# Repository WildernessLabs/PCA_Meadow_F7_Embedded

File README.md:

# PCA_Meadow_F7_Embedded
PCA (Printed Circuit Assembly) design of the Meadow F7 Embedded SMT module.\
Tool: Kicad\
Version: 5.1.6\
Current Revision: B

## Folder Structure
### Home Folder
* Source Files for Current Revsion
### PCB_FAB
Files Required to make the bare PCB
* Gerbers
* Gerbers (zip)
* Stack up 
* Fab Drawing (pdf)
* Pannel Gerbers (to be added)
* Netlist(.d356)
### Assembly
Files required to asseble the PCA, using the bare PCB.
* BOM
* PDF Schematic
* Assembly Drawing (pdf)
* Rendered Pictures
* 3D Model
* pick and place file/pos file (.csv)

## Rev B Change Log
* Retuned USB signals
* Added edge plating to module SMT pads
* Created Fab drawing with pcb fab notes
* Created Assembly Drawing, added assembly notes to it

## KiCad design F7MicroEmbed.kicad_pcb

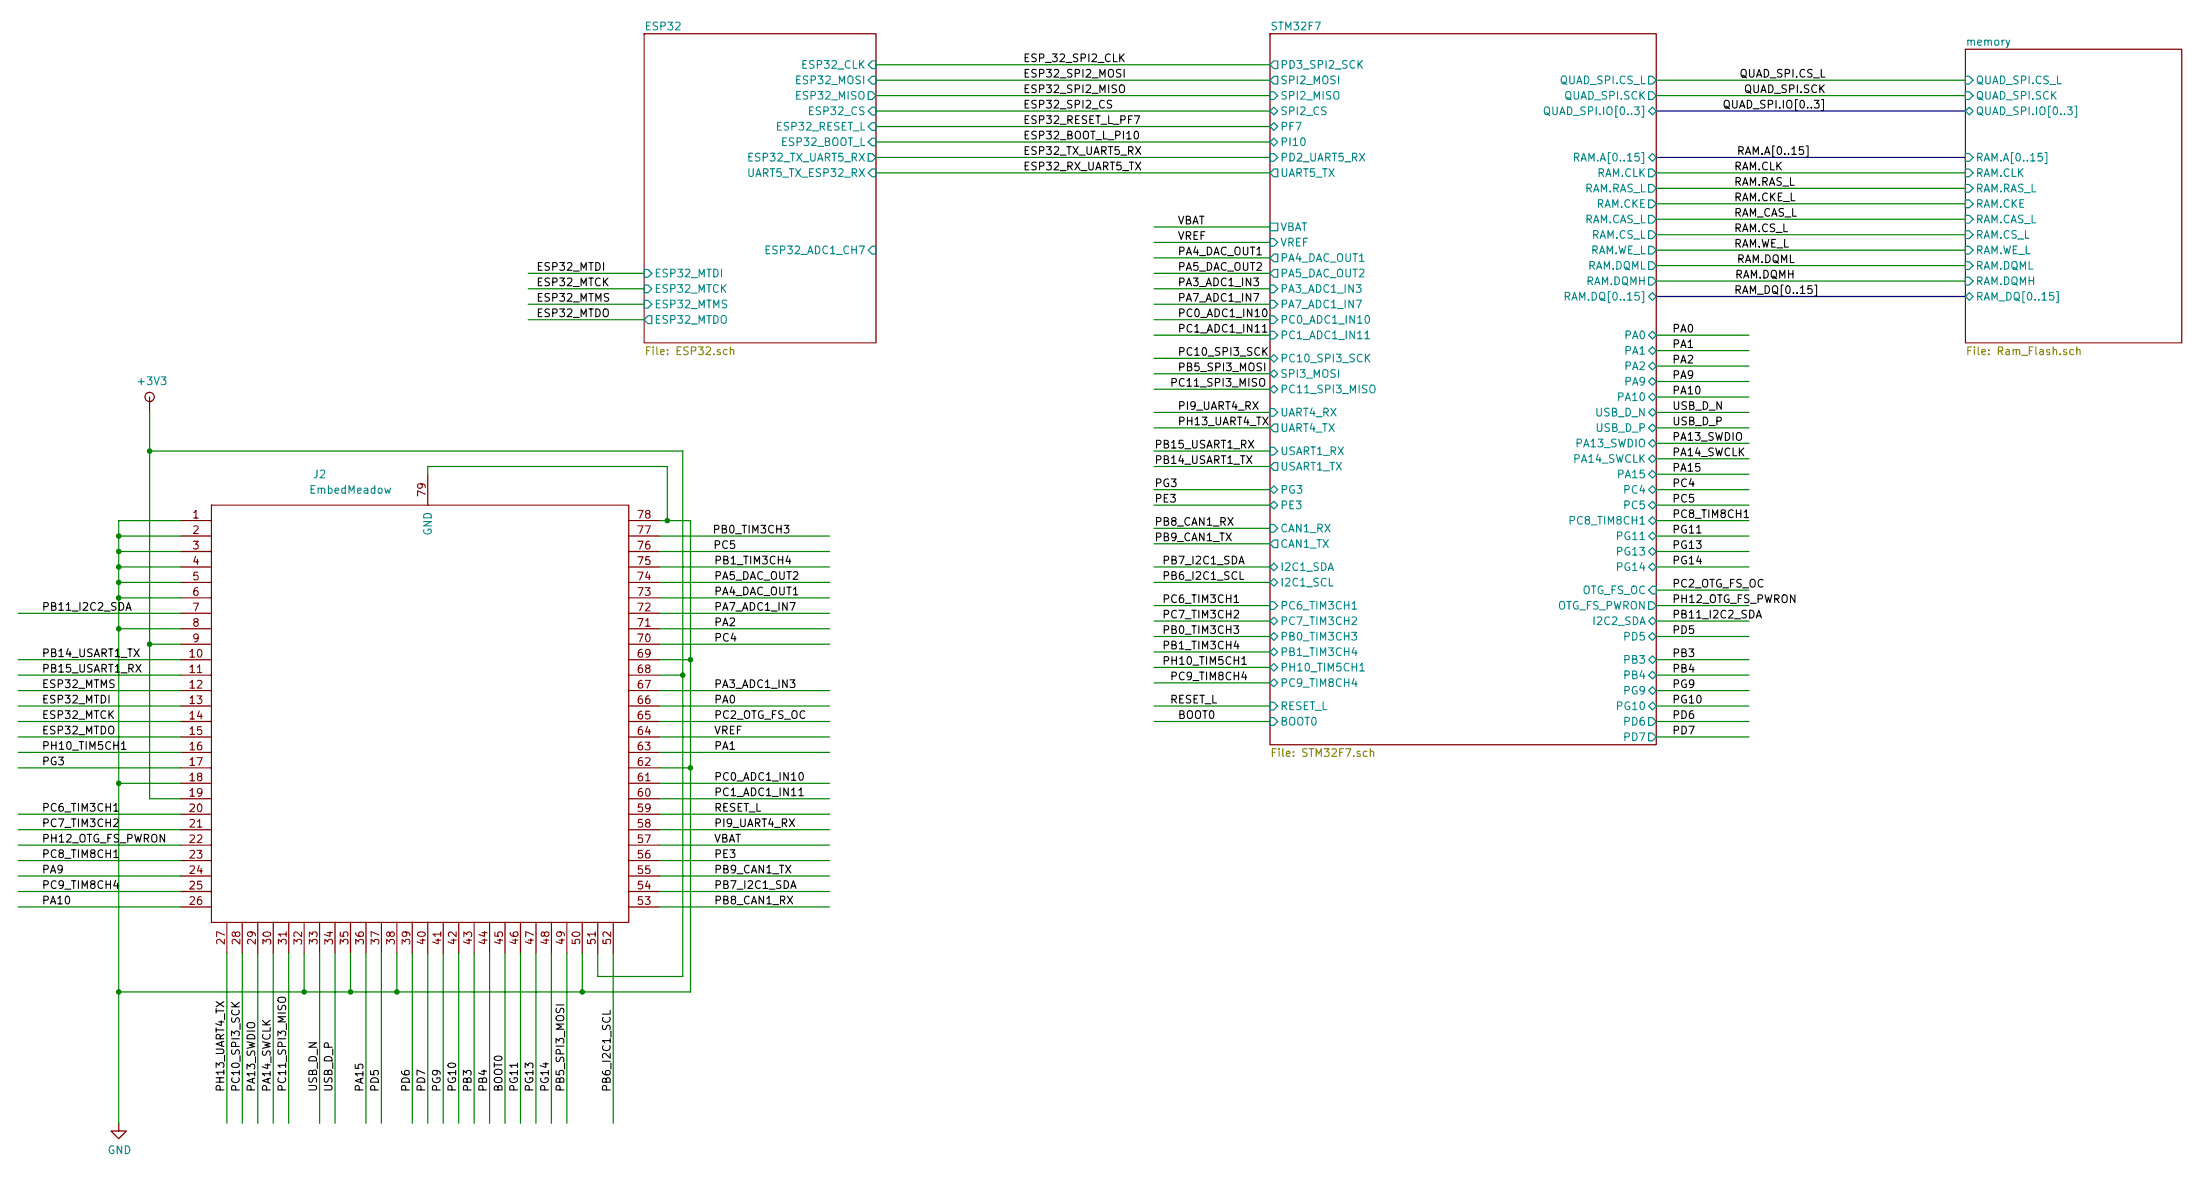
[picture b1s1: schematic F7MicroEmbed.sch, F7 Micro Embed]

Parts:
J2: EmbedMeadow; MeadowEmbeded_OnModule

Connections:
+3V3: J2.9, J2.19, J2.51, J2.68; also elsewhere on the board
/BOOT0: J2.45; also elsewhere on the board
/ESP32_MTCK: J2.14; also elsewhere on the board
/ESP32_MTDI: J2.13; also elsewhere on the board
/ESP32_MTDO: J2.15; also elsewhere on the board
/ESP32_MTMS: J2.12; also elsewhere on the board
/PA0: J2.66; also elsewhere on the board
/PA1: J2.63; also elsewhere on the board
/PA2: J2.71; also elsewhere on the board
/PA3_ADC1_IN3: J2.67; also elsewhere on the board
/PA4_DAC_OUT1: J2.73; also elsewhere on the board
/PA5_DAC_OUT2: J2.74; also elsewhere on the board
/PA7_ADC1_IN7: J2.72; also elsewhere on the board
/PA9: J2.24; also elsewhere on the board
/PA10: J2.26; also elsewhere on the board
/PA13_SWDIO: J2.29; also elsewhere on the board
/PA14_SWCLK: J2.30; also elsewhere on the board
/PA15: J2.36; also elsewhere on the board
/PB0_TIM3CH3: J2.77; also elsewhere on the board
/PB1_TIM3CH4: J2.75; also elsewhere on the board
/PB3: J2.43; also elsewhere on the board
/PB4: J2.44; also elsewhere on the board
/PB5_SPI3_MOSI: J2.49; also elsewhere on the board
/PB6_I2C1_SCL: J2.52; also elsewhere on the board
/PB7_I2C1_SDA: J2.54; also elsewhere on the board
/PB8_CAN1_RX: J2.53; also elsewhere on the board
/PB9_CAN1_TX: J2.55; also elsewhere on the board
/PB11_I2C2_SDA: J2.7; also elsewhere on the board
/PB14_USART1_TX: J2.10; also elsewhere on the board
/PB15_USART1_RX: J2.11; also elsewhere on the board
/PC0_ADC1_IN10: J2.61; also elsewhere on the board
/PC1_ADC1_IN11: J2.60; also elsewhere on the board
/PC2_OTG_FS_OC: J2.65; also elsewhere on the board
/PC4: J2.70; also elsewhere on the board
/PC5: J2.76; also elsewhere on the board
/PC6_TIM3CH1: J2.20; also elsewhere on the board
/PC7_TIM3CH2: J2.21; also elsewhere on the board
/PC8_TIM8CH1: J2.23; also elsewhere on the board
/PC9_TIM8CH4: J2.25; also elsewhere on the board
/PC10_SPI3_SCK: J2.28; also elsewhere on the board
/PC11_SPI3_MISO: J2.31; also elsewhere on the board
/PD5: J2.37; also elsewhere on the board
/PD6: J2.39; also elsewhere on the board
/PD7: J2.40; also elsewhere on the board
/PE3: J2.56; also elsewhere on the board
/PG3: J2.17; also elsewhere on the board
/PG9: J2.41; also elsewhere on the board
/PG10: J2.42; also elsewhere on the board
/PG11: J2.46; also elsewhere on the board
/PG13: J2.47; also elsewhere on the board
/PG14: J2.48; also elsewhere on the board
/PH10_TIM5CH1: J2.16; also elsewhere on the board
/PH12_OTG_FS_PWRON: J2.22; also elsewhere on the board
/PH13_UART4_TX: J2.27; also elsewhere on the board
/PI9_UART4_RX: J2.58; also elsewhere on the board
/RESET_L: J2.59; also elsewhere on the board
/USB_D_N: J2.33; also elsewhere on the board
/USB_D_P: J2.34; also elsewhere on the board
/VBAT: J2.57; also elsewhere on the board
/VREF: J2.64; also elsewhere on the board
GND: J2.1, J2.2, J2.3, J2.4, J2.5, J2.6, J2.8, J2.18, J2.32, J2.35, J2.38, J2.50, J2.62, J2.69, J2.78, J2.79 (GND); also elsewhere on the board

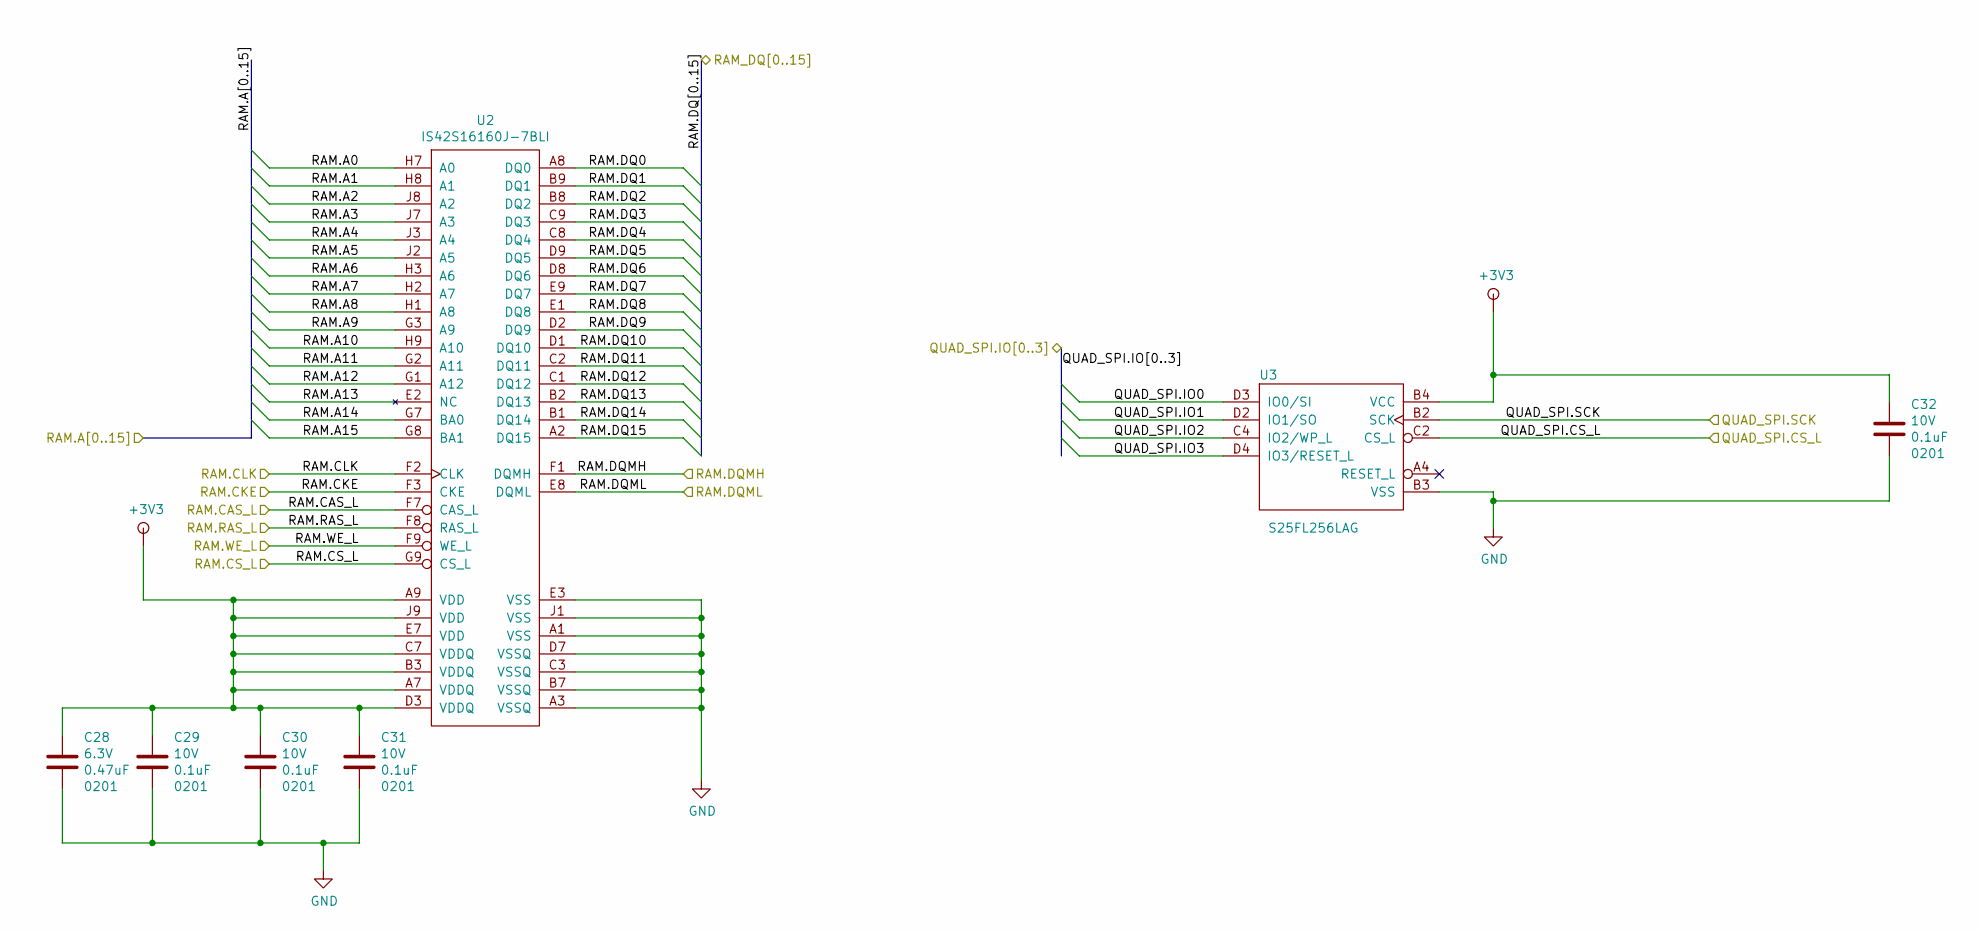
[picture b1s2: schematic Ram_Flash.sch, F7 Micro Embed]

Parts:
C28: C_0201_0.47UF_6.3V_X5R; C_0201; Voltage 6.3V; Tolerance 10%
C29, C30, C31, C32: C_0201_0.1UF_10V_X5R; C_0201; Voltage 10V; Tolerance 10%
U2: IS42S16160J-7BLI; TFBGA-54
U3: S25FL256LAG; BGA24C100P6X4_800X600X120N

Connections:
+3V3: C28.1, C29.1, C30.1, C31.1, C32.1, U2.A7 (VDDQ), U2.A9 (VDD), U2.B3 (VDDQ), U2.C7 (VDDQ), U2.D3 (VDDQ), U2.E7 (VDD), U2.J9 (VDD), U3.B4 (VCC); also elsewhere on the board
/QUAD_SPI.CS_L: U3.C2 (CS_L); also elsewhere on the board
/QUAD_SPI.SCK: U3.B2 (SCK); also elsewhere on the board
/RAM.CKE_L: U2.F3 (CKE); also elsewhere on the board
/RAM.CLK: U2.F2 (CLK); also elsewhere on the board
/RAM.CS_L: U2.G9 (CS_L); also elsewhere on the board
/RAM.DQMH: U2.F1 (DQMH); also elsewhere on the board
/RAM.DQML: U2.E8 (DQML); also elsewhere on the board
/RAM.RAS_L: U2.F8 (RAS_L); also elsewhere on the board
/RAM.WE_L: U2.F9 (WE_L); also elsewhere on the board
/RAM_CAS_L: U2.F7 (CAS_L); also elsewhere on the board
/STM32F7/QUAD_SPI.IO0: U3.D3 (IO0/SI); also elsewhere on the board
/STM32F7/QUAD_SPI.IO1: U3.D2 (IO1/SO); also elsewhere on the board
/STM32F7/QUAD_SPI.IO2: U3.C4 (IO2/WP_L); also elsewhere on the board
/STM32F7/QUAD_SPI.IO3: U3.D4 (IO3/RESET_L); also elsewhere on the board
/STM32F7/RAM.A0: U2.H7 (A0); also elsewhere on the board
/STM32F7/RAM.A1: U2.H8 (A1); also elsewhere on the board
/STM32F7/RAM.A2: U2.J8 (A2); also elsewhere on the board
/STM32F7/RAM.A3: U2.J7 (A3); also elsewhere on the board
/STM32F7/RAM.A4: U2.J3 (A4); also elsewhere on the board
/STM32F7/RAM.A5: U2.J2 (A5); also elsewhere on the board
/STM32F7/RAM.A6: U2.H3 (A6); also elsewhere on the board
/STM32F7/RAM.A7: U2.H2 (A7); also elsewhere on the board
/STM32F7/RAM.A8: U2.H1 (A8); also elsewhere on the board
/STM32F7/RAM.A9: U2.G3 (A9); also elsewhere on the board
/STM32F7/RAM.A10: U2.H9 (A10); also elsewhere on the board
/STM32F7/RAM.A11: U2.G2 (A11); also elsewhere on the board
/STM32F7/RAM.A12: U2.G1 (A12); also elsewhere on the board
/STM32F7/RAM.A14: U2.G7 (BA0); also elsewhere on the board
/STM32F7/RAM.A15: U2.G8 (BA1); also elsewhere on the board
/STM32F7/RAM.DQ0: U2.A8 (DQ0); also elsewhere on the board
/STM32F7/RAM.DQ1: U2.B9 (DQ1); also elsewhere on the board
/STM32F7/RAM.DQ2: U2.B8 (DQ2); also elsewhere on the board
/STM32F7/RAM.DQ3: U2.C9 (DQ3); also elsewhere on the board
/STM32F7/RAM.DQ4: U2.C8 (DQ4); also elsewhere on the board
/STM32F7/RAM.DQ5: U2.D9 (DQ5); also elsewhere on the board
/STM32F7/RAM.DQ6: U2.D8 (DQ6); also elsewhere on the board
/STM32F7/RAM.DQ7: U2.E9 (DQ7); also elsewhere on the board
/STM32F7/RAM.DQ8: U2.E1 (DQ8); also elsewhere on the board
/STM32F7/RAM.DQ9: U2.D2 (DQ9); also elsewhere on the board
/STM32F7/RAM.DQ10: U2.D1 (DQ10); also elsewhere on the board
/STM32F7/RAM.DQ11: U2.C2 (DQ11); also elsewhere on the board
/STM32F7/RAM.DQ12: U2.C1 (DQ12); also elsewhere on the board
/STM32F7/RAM.DQ13: U2.B2 (DQ13); also elsewhere on the board
/STM32F7/RAM.DQ14: U2.B1 (DQ14); also elsewhere on the board
/STM32F7/RAM.DQ15: U2.A2 (DQ15); also elsewhere on the board
/memory/RAM.A13: U2.E2 (NC)
GND: C28.2, C29.2, C30.2, C31.2, C32.2, U2.A1 (VSS), U2.A3 (VSSQ), U2.B7 (VSSQ), U2.C3 (VSSQ), U2.D7 (VSSQ), U2.E3 (VSS), U2.J1 (VSS), U3.B3 (VSS); also elsewhere on the board

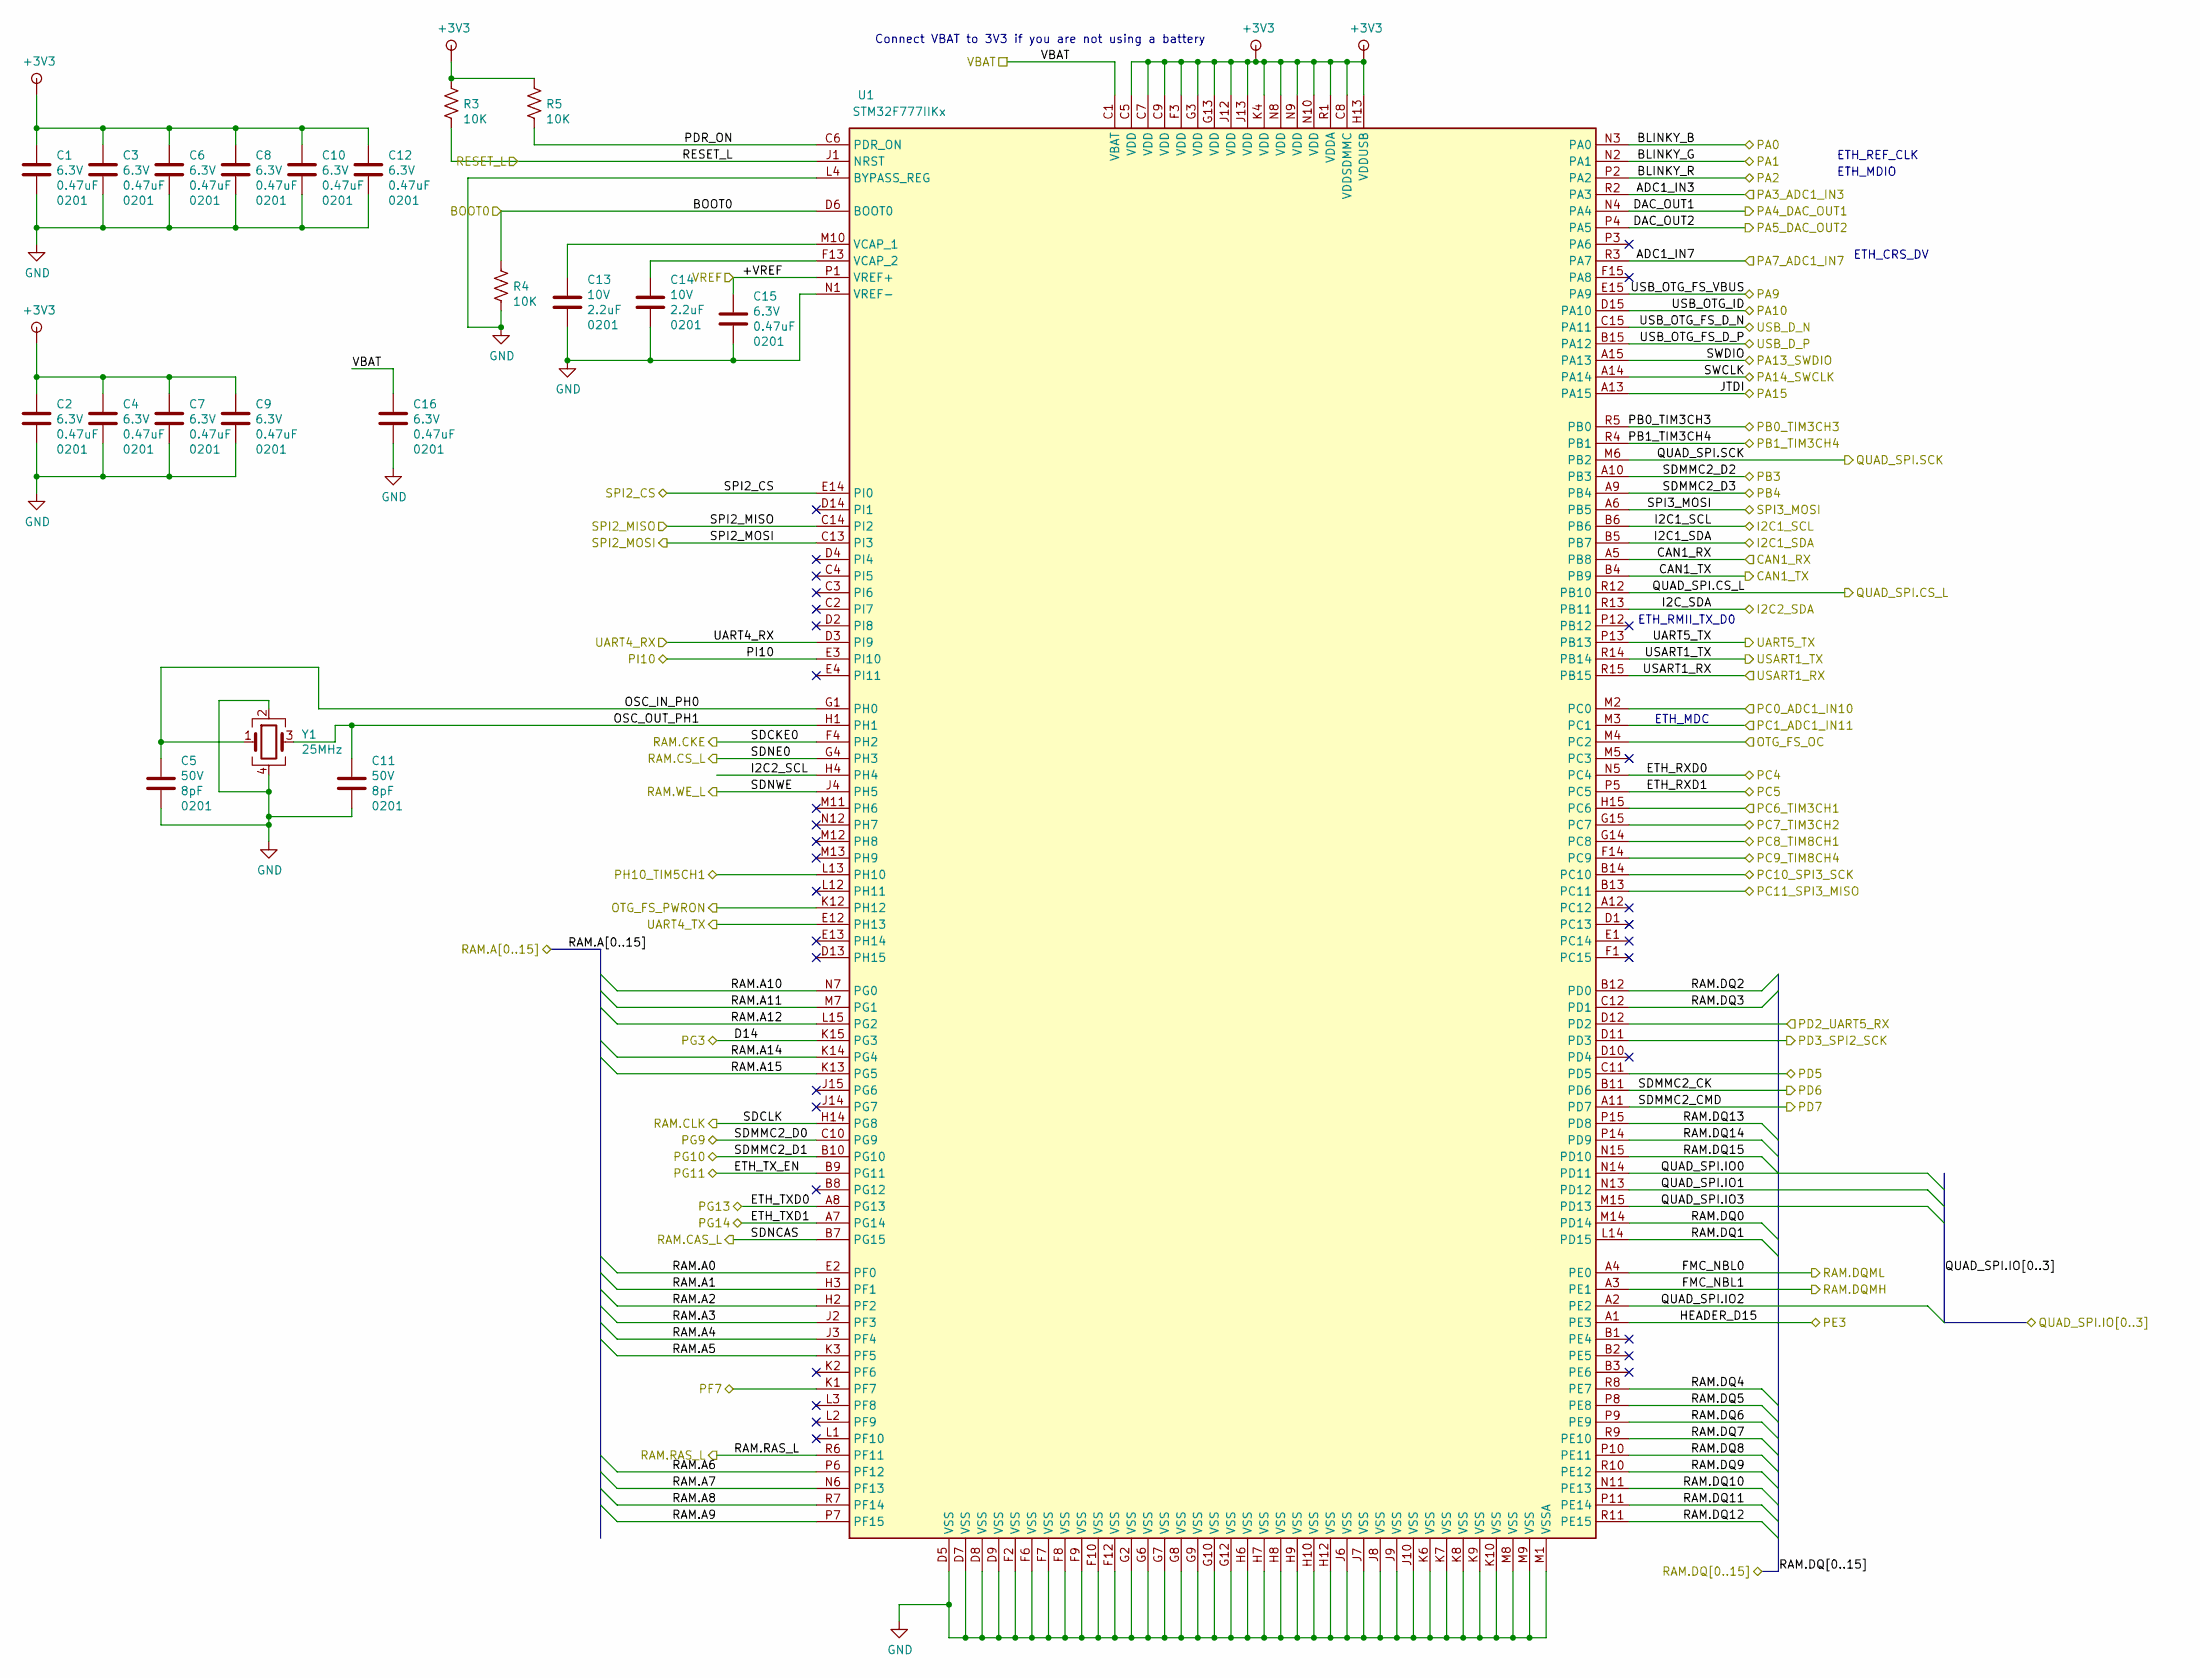
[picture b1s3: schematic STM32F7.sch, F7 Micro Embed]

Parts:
C1, C2, C3, C4, C6, C7, C8, C9, C10, C12, C15, C16: C_0201_0.47UF_6.3V_X5R; C_0201; Voltage 6.3V; Tolerance 10%
C5, C11: C_0201_8pF_50V_C0G; C_0201; Voltage 50V; Tolerance 0.5pF
C13, C14: C_0201_2.2UF_10V_X5R; C_0201; Voltage 10V; Tolerance 10%
R3, R4, R5: R_10K_1%_0201; R_0201
U1: STM32F777IIKx; UFBGA-201_10x10mm_Layout15x15_P0.65mm
Y1: ABM12W-25.0000MHZ-6-B1U-T3; XTAL_ABM12W-24.0000MHZ-6-B1U-T3

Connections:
+3V3: C1.1, C2.1, C3.1, C4.1, C6.1, C7.1, C8.1, C9.1, C10.1, C12.1, R3.1, R5.1, U1.C5 (VDD), U1.C7 (VDD), U1.C8 (VDDSDMMC), U1.C9 (VDD), U1.F3 (VDD), U1.G3 (VDD), U1.G13 (VDD), U1.H13 (VDDUSB), U1.J12 (VDD), U1.J13 (VDD), U1.K4 (VDD), U1.N8 (VDD), U1.N9 (VDD), U1.N10 (VDD), U1.R1 (VDDA); also elsewhere on the board
/BOOT0: R4.1, U1.D6 (BOOT0); also elsewhere on the board
/ESP32_BOOT_L_PI10: U1.E3 (PI10); also elsewhere on the board
/ESP32_RESET_L_PF7: U1.K1 (PF7); also elsewhere on the board
/ESP32_RX_UART5_TX: U1.P13 (PB13); also elsewhere on the board
/ESP32_SPI2_CS: U1.E14 (PI0); also elsewhere on the board
/ESP32_SPI2_MISO: U1.C14 (PI2); also elsewhere on the board
/ESP32_SPI2_MOSI: U1.C13 (PI3); also elsewhere on the board
/ESP32_TX_UART5_RX: U1.D12 (PD2); also elsewhere on the board
/ESP_32_SPI2_CLK: U1.D11 (PD3); also elsewhere on the board
/PA0: U1.N3 (PA0); also elsewhere on the board
/PA1: U1.N2 (PA1); also elsewhere on the board
/PA2: U1.P2 (PA2); also elsewhere on the board
/PA3_ADC1_IN3: U1.R2 (PA3); also elsewhere on the board
/PA4_DAC_OUT1: U1.N4 (PA4); also elsewhere on the board
/PA5_DAC_OUT2: U1.P4 (PA5); also elsewhere on the board
/PA7_ADC1_IN7: U1.R3 (PA7); also elsewhere on the board
/PA9: U1.E15 (PA9); also elsewhere on the board
/PA10: U1.D15 (PA10); also elsewhere on the board
/PA13_SWDIO: U1.A15 (PA13); also elsewhere on the board
/PA14_SWCLK: U1.A14; also elsewhere on the board
/PA15: U1.A13 (PA15); also elsewhere on the board
/PB0_TIM3CH3: U1.R5 (PB0); also elsewhere on the board
/PB1_TIM3CH4: U1.R4 (PB1); also elsewhere on the board
/PB3: U1.A10 (PB3); also elsewhere on the board
/PB4: U1.A9 (PB4); also elsewhere on the board
/PB5_SPI3_MOSI: U1.A6 (PB5); also elsewhere on the board
/PB6_I2C1_SCL: U1.B6; also elsewhere on the board
/PB7_I2C1_SDA: U1.B5 (PB7); also elsewhere on the board
/PB8_CAN1_RX: U1.A5 (PB8); also elsewhere on the board
/PB9_CAN1_TX: U1.B4 (PB9); also elsewhere on the board
/PB11_I2C2_SDA: U1.R13 (PB11); also elsewhere on the board
/PB14_USART1_TX: U1.R14 (PB14); also elsewhere on the board
/PB15_USART1_RX: U1.R15 (PB15); also elsewhere on the board
/PC0_ADC1_IN10: U1.M2 (PC0); also elsewhere on the board
/PC1_ADC1_IN11: U1.M3 (PC1); also elsewhere on the board
/PC2_OTG_FS_OC: U1.M4 (PC2); also elsewhere on the board
/PC4: U1.N5 (PC4); also elsewhere on the board
/PC5: U1.P5 (PC5); also elsewhere on the board
/PC6_TIM3CH1: U1.H15 (PC6); also elsewhere on the board
/PC7_TIM3CH2: U1.G15 (PC7); also elsewhere on the board
/PC8_TIM8CH1: U1.G14 (PC8); also elsewhere on the board
/PC9_TIM8CH4: U1.F14 (PC9); also elsewhere on the board
/PC10_SPI3_SCK: U1.B14 (PC10); also elsewhere on the board
/PC11_SPI3_MISO: U1.B13 (PC11); also elsewhere on the board
/PD5: U1.C11 (PD5); also elsewhere on the board
/PD6: U1.B11 (PD6); also elsewhere on the board
/PD7: U1.A11 (PD7); also elsewhere on the board
/PE3: U1.A1 (PE3); also elsewhere on the board
/PG3: U1.K15 (PG3); also elsewhere on the board
/PG9: U1.C10 (PG9); also elsewhere on the board
/PG10: U1.B10 (PG10); also elsewhere on the board
/PG11: U1.B9 (PG11); also elsewhere on the board
/PG13: U1.A8 (PG13); also elsewhere on the board
/PG14: U1.A7 (PG14); also elsewhere on the board
/PH10_TIM5CH1: U1.L13 (PH10); also elsewhere on the board
/PH12_OTG_FS_PWRON: U1.K12 (PH12); also elsewhere on the board
/PH13_UART4_TX: U1.E12 (PH13); also elsewhere on the board
/PI9_UART4_RX: U1.D3 (PI9); also elsewhere on the board
/QUAD_SPI.CS_L: U1.R12 (PB10); also elsewhere on the board
/QUAD_SPI.SCK: U1.M6 (PB2); also elsewhere on the board
/RAM.CKE_L: U1.F4 (PH2); also elsewhere on the board
/RAM.CLK: U1.H14 (PG8); also elsewhere on the board
/RAM.CS_L: U1.G4 (PH3); also elsewhere on the board
/RAM.DQMH: U1.A3 (PE1); also elsewhere on the board
/RAM.DQML: U1.A4 (PE0); also elsewhere on the board
/RAM.RAS_L: U1.R6 (PF11); also elsewhere on the board
/RAM.WE_L: U1.J4 (PH5); also elsewhere on the board
/RAM_CAS_L: U1.B7 (PG15); also elsewhere on the board
/RESET_L: R3.2, U1.J1 (NRST); also elsewhere on the board
/STM32F7/I2C2_SCL: U1.H4
/STM32F7/OSC_IN_PH0: C5.1, U1.G1 (PH0), Y1.1
/STM32F7/OSC_OUT_PH1: C11.1, U1.H1, Y1.3
/STM32F7/PDR_ON: R5.2, U1.C6 (PDR_ON)
/STM32F7/QUAD_SPI.IO0: U1.N14 (PD11); also elsewhere on the board
/STM32F7/QUAD_SPI.IO1: U1.N13 (PD12); also elsewhere on the board
/STM32F7/QUAD_SPI.IO2: U1.A2 (PE2); also elsewhere on the board
/STM32F7/QUAD_SPI.IO3: U1.M15 (PD13); also elsewhere on the board
/STM32F7/RAM.A0: U1.E2 (PF0); also elsewhere on the board
/STM32F7/RAM.A1: U1.H3 (PF1); also elsewhere on the board
/STM32F7/RAM.A2: U1.H2 (PF2); also elsewhere on the board
/STM32F7/RAM.A3: U1.J2 (PF3); also elsewhere on the board
/STM32F7/RAM.A4: U1.J3 (PF4); also elsewhere on the board
/STM32F7/RAM.A5: U1.K3 (PF5); also elsewhere on the board
/STM32F7/RAM.A6: U1.P6 (PF12); also elsewhere on the board
/STM32F7/RAM.A7: U1.N6 (PF13); also elsewhere on the board
/STM32F7/RAM.A8: U1.R7 (PF14); also elsewhere on the board
/STM32F7/RAM.A9: U1.P7 (PF15); also elsewhere on the board
/STM32F7/RAM.A10: U1.N7 (PG0); also elsewhere on the board
/STM32F7/RAM.A11: U1.M7 (PG1); also elsewhere on the board
/STM32F7/RAM.A12: U1.L15 (PG2); also elsewhere on the board
/STM32F7/RAM.A14: U1.K14 (PG4); also elsewhere on the board
/STM32F7/RAM.A15: U1.K13 (PG5); also elsewhere on the board
/STM32F7/RAM.DQ0: U1.M14 (PD14); also elsewhere on the board
/STM32F7/RAM.DQ1: U1.L14 (PD15); also elsewhere on the board
/STM32F7/RAM.DQ2: U1.B12 (PD0); also elsewhere on the board
/STM32F7/RAM.DQ3: U1.C12 (PD1); also elsewhere on the board
/STM32F7/RAM.DQ4: U1.R8 (PE7); also elsewhere on the board
/STM32F7/RAM.DQ5: U1.P8 (PE8); also elsewhere on the board
/STM32F7/RAM.DQ6: U1.P9 (PE9); also elsewhere on the board
/STM32F7/RAM.DQ7: U1.R9 (PE10); also elsewhere on the board
/STM32F7/RAM.DQ8: U1.P10 (PE11); also elsewhere on the board
/STM32F7/RAM.DQ9: U1.R10 (PE12); also elsewhere on the board
/STM32F7/RAM.DQ10: U1.N11 (PE13); also elsewhere on the board
/STM32F7/RAM.DQ11: U1.P11 (PE14); also elsewhere on the board
/STM32F7/RAM.DQ12: U1.R11 (PE15); also elsewhere on the board
/STM32F7/RAM.DQ13: U1.P15 (PD8); also elsewhere on the board
/STM32F7/RAM.DQ14: U1.P14 (PD9); also elsewhere on the board
/STM32F7/RAM.DQ15: U1.N15 (PD10); also elsewhere on the board
/USB_D_N: U1.C15 (PA11); also elsewhere on the board
/USB_D_P: U1.B15 (PA12); also elsewhere on the board
/VBAT: C16.1, U1.C1 (VBAT); also elsewhere on the board
/VREF: C15.1, U1.P1 (VREF+); also elsewhere on the board
GND: C1.2, C2.2, C3.2, C4.2, C5.2, C6.2, C7.2, C8.2, C9.2, C10.2, C11.2, C12.2, C13.2, C14.2, C15.2, C16.2, R4.2, U1.D5 (VSS), U1.D7 (VSS), U1.D8 (VSS), U1.D9 (VSS), U1.F2 (VSS), U1.F6 (VSS), U1.F7 (VSS), U1.F8 (VSS), U1.F9 (VSS), U1.F10 (VSS), U1.F12 (VSS), U1.G2 (VSS), U1.G6 (VSS), U1.G7 (VSS), U1.G8 (VSS), U1.G9 (VSS), U1.G10 (VSS), U1.G12 (VSS), U1.H6 (VSS), U1.H7 (VSS), U1.H8 (VSS), U1.H9 (VSS), U1.H10 (VSS), U1.H12 (VSS), U1.J6 (VSS), U1.J7 (VSS), U1.J8 (VSS), U1.J9 (VSS), U1.J10 (VSS), U1.K6 (VSS), U1.K7 (VSS), U1.K8 (VSS), U1.K9 (VSS), U1.K10 (VSS), U1.L4 (BYPASS_REG), U1.M1 (VSSA), U1.M8 (VSS), U1.M9 (VSS), U1.N1 (VREF-), Y1.2, Y1.4; also elsewhere on the board
unnamed: C13.1, U1.M10 (VCAP_1)
unnamed: C14.1, U1.F13 (VCAP_2)

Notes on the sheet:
Connect VBAT to 3V3 if you are not using a battery
ETH_MDC
ETH_CRS_DV
ETH_MDIO
ETH_REF_CLK
ETH_RMII_TX_D0

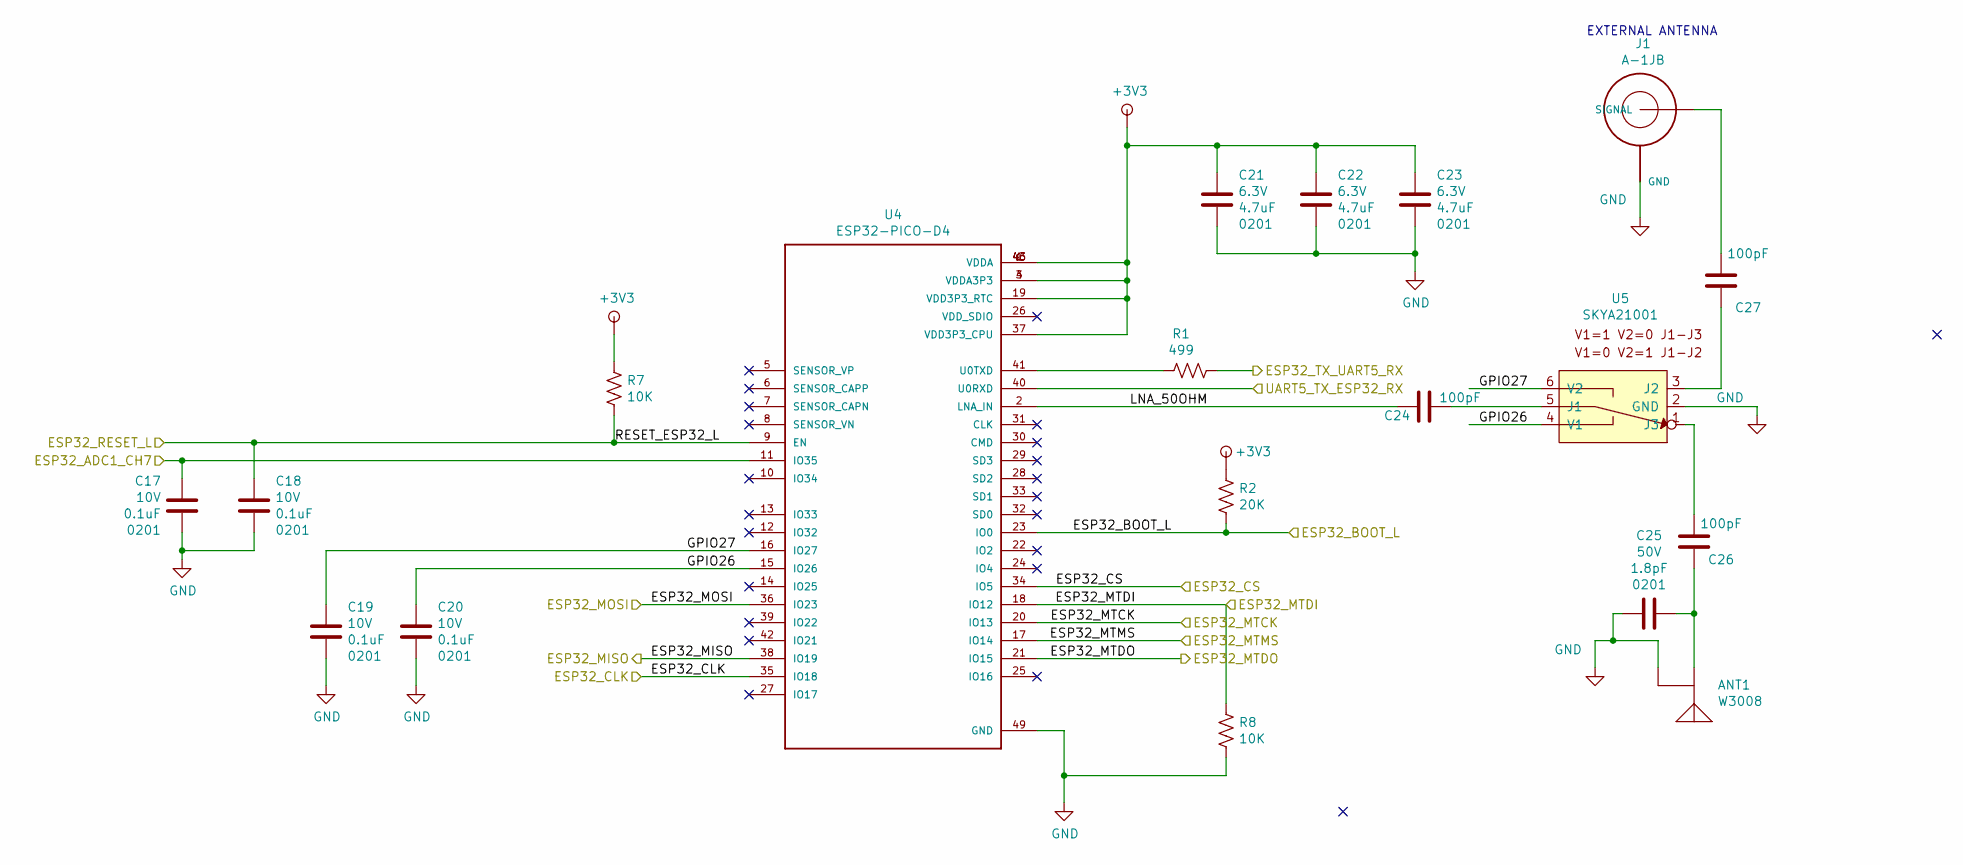
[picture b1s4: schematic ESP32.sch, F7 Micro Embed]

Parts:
ANT1: W3008; ANTENNA_W3008
C17, C18, C19, C20: C_0201_0.1UF_10V_X5R; C_0201; Voltage 10V; Tolerance 10%
C21, C22, C23: C_0201_4.7UF_6.3V_X5R; C_0201; Voltage 6.3V; Tolerance 20%
C24, C26, C27: C_0201_100PF_50V_C0G; C_0201; Voltage 50V; Tolerance 5%
C25: C_0201_1.8pF_50V_C0G; C_0201; Voltage 50V; Tolerance 0.25pF
J1: A-1JB; AMPHENOL_A-1JB
R1: R_499_1%_0201; R_0201
R2: R_20K_1%_0201; R_0201
R7, R8: R_10K_1%_0201; R_0201
U4: ESP32-PICO-D4; PQFN50P700X700X104-49N
U5: SKYA21001; SOT-363_SC-70-6

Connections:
+3V3: C21.1, C22.1, C23.1, R2.1, R7.1, U4.1 (VDDA), U4.3 (VDDA3P3), U4.4 (VDDA3P3), U4.19 (VDD3P3_RTC), U4.37 (VDD3P3_CPU), U4.43 (VDDA), U4.46 (VDDA); also elsewhere on the board
/ESP32/ESP32_ADC1_CH7: C17.2, U4.11 (IO35)
/ESP32/GPIO26: C20.1, U4.15 (IO26), U5.4 (V1)
/ESP32/GPIO27: C19.1, U4.16 (IO27), U5.6 (V2)
/ESP32/LNA_50OHM: C24.2, U4.2 (LNA_IN)
/ESP32_BOOT_L_PI10: R2.2, U4.23 (IO0); also elsewhere on the board
/ESP32_MTCK: U4.20 (IO13); also elsewhere on the board
/ESP32_MTDI: R8.1, U4.18 (IO12); also elsewhere on the board
/ESP32_MTDO: U4.21 (IO15); also elsewhere on the board
/ESP32_MTMS: U4.17 (IO14); also elsewhere on the board
/ESP32_RESET_L_PF7: C18.1, R7.2, U4.9 (EN); also elsewhere on the board
/ESP32_RX_UART5_TX: U4.40 (U0RXD); also elsewhere on the board
/ESP32_SPI2_CS: U4.34 (IO5); also elsewhere on the board
/ESP32_SPI2_MISO: U4.38 (IO19); also elsewhere on the board
/ESP32_SPI2_MOSI: U4.36 (IO23); also elsewhere on the board
/ESP32_TX_UART5_RX: R1.1; also elsewhere on the board
/ESP_32_SPI2_CLK: U4.35 (IO18); also elsewhere on the board
GND: ANT1.G1 (GND), ANT1.G2 (GND), C17.1, C18.2, C19.2, C20.2, C21.2, C22.2, C23.2, C25.2, J1.GND1 (GND), J1.GND2 (GND), J1.OPTIONAL_GND (GND), R8.2, U4.49 (GND), U5.2 (GND); also elsewhere on the board
unnamed: ANT1.FEED, C25.1, C26.1
unnamed: C24.1, U5.5 (J1)
unnamed: C26.2, U5.1 (J3)
unnamed: C27.1, U5.3 (J2)
unnamed: C27.2, J1.SIGNAL
unnamed: R1.2, U4.41 (U0TXD)

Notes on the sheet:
EXTERNAL ANTENNA

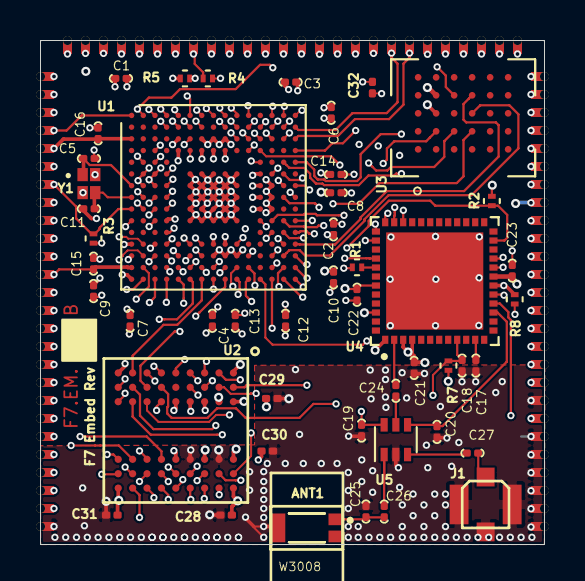
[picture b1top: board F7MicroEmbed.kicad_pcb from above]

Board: 8 copper layers, 28.0 x 28.0 mm, 48 parts (0 on the bottom side), 129 nets.

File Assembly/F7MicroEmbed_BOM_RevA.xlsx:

Quantity | Reference | PN | MF | MF2 | PN2 | Value | Size | Tolerance | Voltage | Res_value | Footprint
1 | ANT1 | W3008 | PulseLarsen Antennas |  |  | W3008 |  |  |  |  | SLJ_SMT:ANTENNA_W3008
2 | C13 C14 | GRM033R61A225KE47D | Murata Electronics North America | Samsung Electro-Mechanics | CL03A225MP3CRNC | C_0201_2.2UF_10V_X5R | 201 | 0.1 | 10V |  | Capacitors_SMD:C_0201
3 | C21 C22 C23 | GRM035R60J475ME15D | Murata Electronics North America |  |  | C_0201_4.7UF_6.3V_X5R | 201 | 0.2 | 6.3V |  | Capacitors_SMD:C_0201
1 | C25 | GRM0335C1H1R8CA01D | Murata Electronics North America | Yageo | CC0201BRNPO9BN1R8 | C_0201_1.8pF_50V_C0G | 201 | 0.25pF | 50V |  | Capacitors_SMD:C_0201
3 | C27 C26 C24 | GRM0335C1H101JA01D | Murata Electronics North America | Vishay | VJ0201A101JXACW1BC-ND | C_0201_100PF_50V_C0G | 201 | 0.05 | 50V |  | Capacitors_SMD:C_0201
13 | C1 C28 C3 C8 C10 C15 C6 C12 C2 C4 C9 C7 C16 | GRM033R60J474KE90D | Murata Electronics North America | Samsung Electro-Mechanics | CL03A474KQ3NNNH | C_0201_0.47UF_6.3V_X5R | 201 | 0.1 | 6.3V |  | Capacitors_SMD:C_0201
8 | C30 C31 C29 C32 C17 C19 C20 C18 | GRM033R61A104KE15D | Murata Electronics North America | Samsung Electro-Mechanics | CL03A104KP3NNNC | C_0201_0.1UF_10V_X5R | 201 | 0.1 | 10V |  | Capacitors_SMD:C_0201
2 | C5 C11 | GRM0335C1H8R0DA01J | Murata Electronics North America | Yageo | CC0201DRNPO9BN8R0 | C_0201_8pF_50V_C0G | 201 | 0.5pF | 50V |  | Capacitors_SMD:C_0201
1 | J1 | A-1JB | Amphenol RF Division |  |  | A-1JB |  |  |  |  | SLJ_Connectors:AMPHENOL_A-1JB
1 | R1 | ERJ-1GNF4990C | Panasonic Electronic Components |  |  | R_499_1%_0201 |  |  |  | 499 | Resistors_SMD:R_0201
1 | R2 | RC0201FR-0720KL | Yageo |  |  | R_20K_1%_0201 |  |  |  | 20K | Resistors_SMD:R_0201
5 | R3 R4 R5 R8 R7 | RC0201FR-0710KL | Yageo |  |  | R_10K_1%_0201 |  |  |  | 10K | Resistors_SMD:R_0201
1 | U1 | STM32F777IIK6 | STMicroelctronics |  |  | STM32F777IIKx |  |  |  |  | Package_BGA:UFBGA-201_10x10mm_Layout15x15_P0.65mm
1 | U2 | IS42S16160J-7BLI | ISSI, Integrated Silicon Solution Inc |  |  | IS42S16160J-7BLI |  |  |  |  | SLJ_BGA:TFBGA-54
1 | U3 | S25FL256LAGBHV030 | Cypress Semiconductor Corp |  |  | S25FL256LAG |  |  |  |  | SLJ_BGA:BGA24C100P6X4_800X600X120N
1 | U4 | ESP32-PICO-D4 | Espressif Systems |  |  | ESP32-PICO-D4 |  |  |  |  | SLJ_QFN:PQFN50P700X700X104-49N
1 | U5 | SKYA21001 | Skyworks Solutions Inc. |  |  | SKYA21001 |  |  |  |  | SLJ_SMT:SOT-363_SC-70-6
1 | Y1 | ABM12W-25.0000MHZ-6-B1U-T3 | Abracon LLC |  |  | ABM12W-25.0000MHZ-6-B1U-T3 |  |  |  |  | SLJ_Crystals_Osc:XTAL_ABM12W-24.0000MHZ-6-B1U-T3

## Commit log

2020-09-26 Added to new repo
2020-10-23 added ds_store crap
2020-11-15 Rev B
    Added Edge plating
    Added Fab notes/drawing
    Add assembly notes/drawing
2020-11-15 Finally work on Rev B
    Gerbers
    Drawings
    ReTunned USB. I believe it was not right before
2020-11-15 Rev B`
    Added Position file
    Gerbers updated
    Updated Readme
2020-11-15 Rev B
    Update Read me
2020-11-28 Updated Step
2020-12-11 Added panalized gerbers
2020-12-14 JTAG swizzle complete
2020-12-20 Updated for with castellations
